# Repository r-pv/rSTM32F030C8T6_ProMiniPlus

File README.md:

# rSTM32F030C8T6 ProMini+
An ST development board based on the STM32F030C8T6 (Clock: 48MHz, Flash: 64Kb, Ram:8Kb) MCU compatible with STM32Duino (Arduino). 

Pinout:

## Files and Folders description

- **RBOARD_F030C8T6** it's the variant board for the STM32 Arduino Core.
- **rSTM32F030C8T6** it's the KiCAD 5.1.2 project.
- **rSTM32F030C8T6.schematic.pdf** the schematic.

## Install

**Update:** STCore v2.0 includes support for this MCU, if you're using STCore v2.0 you don't need to install anything.

- This requires the [STM32 core for arduino](https://github.com/stm32duino/Arduino_Core_STM32/), the ST original.
- I used this [guide to add the board](https://github.com/stm32duino/wiki/wiki/Add-a-new-variant-(board)), you can check it or continue with my suggestions to install the new board.
- Copy the **"RBOARD_F030C8T6"** folder to the Arduino **"variants"** folder, in win7 is located at: **c:\Users\\<USERNAME\>\AppData\Local\Arduino15\packages\STM32\hardware\stm32\1.6.1\variants**
- Edit the **"boards.txt"** file, in win7 is located at a lever up than the "variants" folder, search for the **F030F4** board and add the lines to leave it as I show you next:

```
# DEMO_F030F4 board
# Support: Serial1 (USART1 on PA3, PA2)
GenF0.menu.pnum.DEMO_F030F4=STM32F030F4 Demo board
GenF0.menu.pnum.DEMO_F030F4.upload.maximum_data_size=4096
GenF0.menu.pnum.DEMO_F030F4.upload.maximum_size=16384
GenF0.menu.pnum.DEMO_F030F4.build.mcu=cortex-m0
GenF0.menu.pnum.DEMO_F030F4.build.board=DEMO_F030F4
GenF0.menu.pnum.DEMO_F030F4.build.series=STM32F0xx
GenF0.menu.pnum.DEMO_F030F4.build.product_line=STM32F030x6
GenF0.menu.pnum.DEMO_F030F4.build.variant=DEMO_F030F4
GenF0.menu.pnum.DEMO_F030F4.build.cmsis_lib_gcc=arm_cortexM0l_math

# RBOARD_F030C8T6 board
# Support: Serial1 (USART1 on PA3, PA2)
GenF0.menu.pnum.RBOARD_F030C8T6=STM32F030C8 STProMiniPlus
GenF0.menu.pnum.RBOARD_F030C8T6.upload.maximum_data_size=8192
GenF0.menu.pnum.RBOARD_F030C8T6.upload.maximum_size=65536
GenF0.menu.pnum.RBOARD_F030C8T6.build.mcu=cortex-m0
GenF0.menu.pnum.RBOARD_F030C8T6.build.board=RBOARD_F030C8T6
GenF0.menu.pnum.RBOARD_F030C8T6.build.series=STM32F0xx
GenF0.menu.pnum.RBOARD_F030C8T6.build.product_line=STM32F030x8
GenF0.menu.pnum.RBOARD_F030C8T6.build.variant=RBOARD_F030C8T6
GenF0.menu.pnum.RBOARD_F030C8T6.build.cmsis_lib_gcc=arm_cortexM0l_math
```

## The real board

## Running some tests

The **ProMini+** running the Adafruit ILI9341 library over hardware SPI.

_Video in progress..._

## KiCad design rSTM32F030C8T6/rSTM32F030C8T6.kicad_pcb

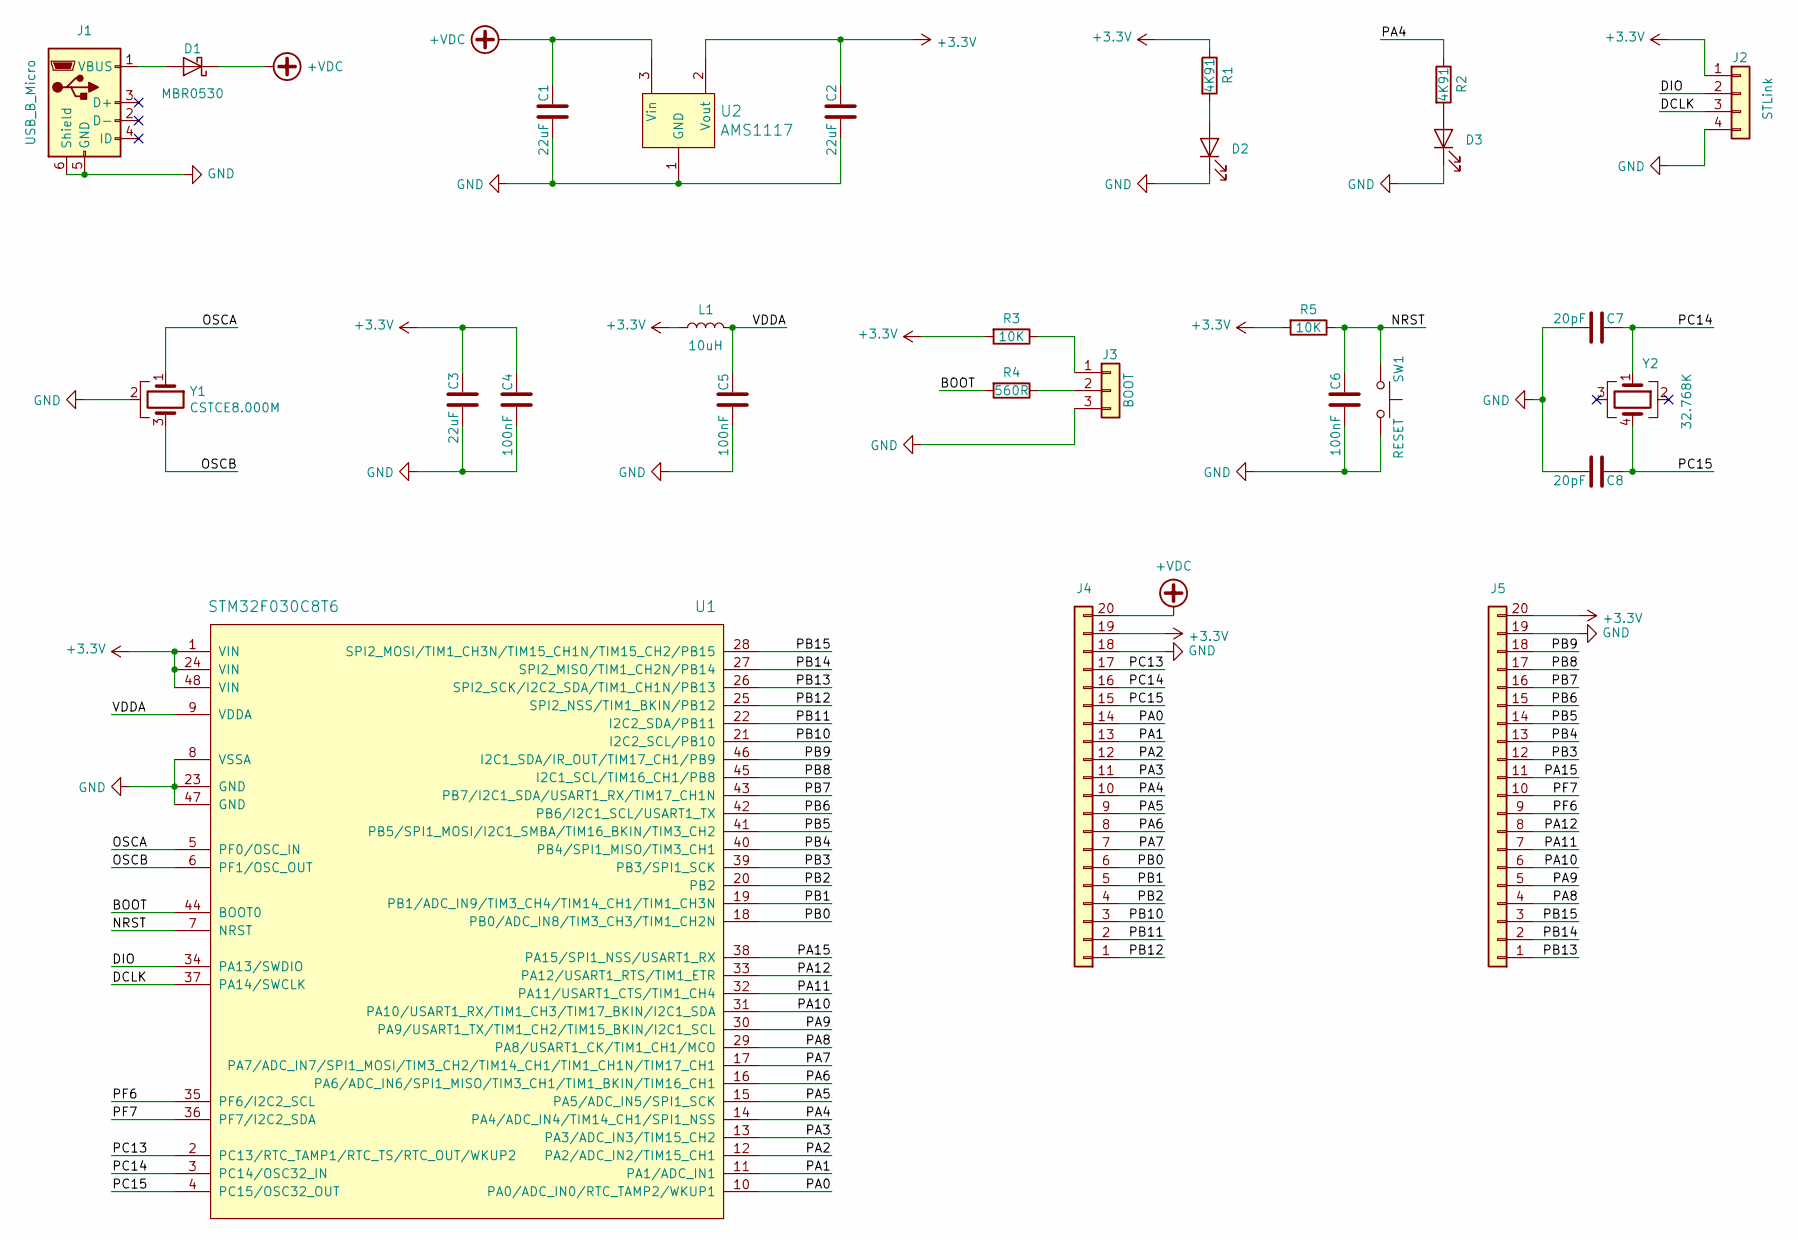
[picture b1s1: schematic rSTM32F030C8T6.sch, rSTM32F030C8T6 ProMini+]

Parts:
C1, C2, C3: 22uF; C_0805
C4, C5, C6: 100nF; C_0805
C7, C8: 20pF; C_0805
D1: MBR0530; D_SOD-123
D2, D3: LED; LED_0805
J1: USB_B_Micro; USB_Micro-B_Molex_47346-0001
J2: STLink; Pin_Header_Straight_1x04_Pitch2.54mm
J3: BOOT; Pin_Header_Straight_1x03_Pitch2.54mm
J4, J5: Pin_Header_Straight_1x20_Pitch2.54mm
L1: 10uH; L_0805
R1, R2: 4K91; R_0603
R3, R5: 10K; R_0603
R4: 560R; R_0603
SW1: RESET; Switch_SMD_5.2x6.4_reset
U1: STM32F030C8T6; LQFP-48_7x7mm_Pitch0.5mm
U2: AMS1117; SOT-223-3_TabPin2
Y1: CSTCE8.000M; Crystal_CSTCE_3pin_3.2x1.3
Y2: 32.768K; Crystal_4pin_SMD_2.5x4.6

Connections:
+3V3: C2.1, C3.1, C4.2, J2.1, J4.19, J5.20, L1.1, R1.1, R3.2, R5.2, U1.1 (VIN), U1.24 (VIN), U1.48 (VIN), U2.2 (Vout)
+VDC: C1.1, D1.1 (K), J4.20, U2.3 (Vin)
/BOOT: R4.2, U1.44 (BOOT0)
/DCLK: J2.3, U1.37 (PA14/SWCLK)
/DIO: J2.2, U1.34 (PA13/SWDIO)
/NRST: C6.1, R5.1, SW1.1, U1.7 (NRST)
/OSCA: U1.5 (PF0/OSC_IN), Y1.1
/OSCB: U1.6 (PF1/OSC_OUT), Y1.3
/PA0: J4.14, U1.10 (PA0/ADC_IN0/RTC_TAMP2/WKUP1)
/PA1: J4.13, U1.11 (PA1/ADC_IN1)
/PA2: J4.12, U1.12 (PA2/ADC_IN2/TIM15_CH1)
/PA3: J4.11, U1.13 (PA3/ADC_IN3/TIM15_CH2)
/PA4: J4.10, R2.1, U1.14 (PA4/ADC_IN4/TIM14_CH1/SPI1_NSS)
/PA5: J4.9, U1.15 (PA5/ADC_IN5/SPI1_SCK)
/PA6: J4.8, U1.16 (PA6/ADC_IN6/SPI1_MISO/TIM3_CH1/TIM1_BKI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)
/PA7: J4.7, U1.17 (PA7/ADC_IN7/SPI1_MOSI/TIM3_CH2/TIM14_CH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)
/PA8: J5.4, U1.29 (PA8/USART1_CK/TIM1_CH1/MCO)
/PA9: J5.5, U1.30 (PA9/USART1_TX/TIM1_CH2/TIM15_BKIN/I2C1_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)
/PA10: J5.6, U1.31 (PA10/USART1_RX/TIM1_CH3/TIM17_BKIN/I2C1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)
/PA11: J5.7, U1.32 (PA11/USART1_CTS/TIM1_CH4)
/PA12: J5.8, U1.33 (PA12/USART1_RTS/TIM1_ETR)
/PA15: J5.11, U1.38 (PA15/SPI1_NSS/USART1_RX)
/PB0: J4.6, U1.18 (PB0/ADC_IN8/TIM3_CH3/TIM1_CH2N)
/PB1: J4.5, U1.19 (PB1/ADC_IN9/TIM3_CH4/TIM14_CH1/TIM1_CH3N)
/PB2: J4.4, U1.20 (PB2)
/PB3: J5.12, U1.39 (PB3/SPI1_SCK)
/PB4: J5.13, U1.40 (PB4/SPI1_MISO/TIM3_CH1)
/PB5: J5.14, U1.41 (PB5/SPI1_MOSI/I2C1_SMBA/TIM16_BKIN/TIM3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)
/PB6: J5.15, U1.42 (PB6/I2C1_SCL/USART1_TX)
/PB7: J5.16, U1.43 (PB7/I2C1_SDA/USART1_RX/TIM17_CH1N)
/PB8: J5.17, U1.45 (I2C1_SCL/TIM16_CH1/PB8)
/PB9: J5.18, U1.46 (I2C1_SDA/IR_OUT/TIM17_CH1/PB9)
/PB10: J4.3, U1.21 (I2C2_SCL/PB10)
/PB11: J4.2, U1.22 (I2C2_SDA/PB11)
/PB12: J4.1, U1.25 (SPI2_NSS/TIM1_BKIN/PB12)
/PB13: J5.1, U1.26 (SPI2_SCK/I2C2_SDA/TIM1_CH1N/PB13)
/PB14: J5.2, U1.27 (SPI2_MISO/TIM1_CH2N/PB14)
/PB15: J5.3, U1.28 (SPI2_MOSI/TIM1_CH3N/TIM15_CH1N/TIM15_CH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)
/PC13: J4.17, U1.2 (PC13/RTC_TAMP1/RTC_TS/RTC_OUT/WKUP2)
/PC14: C7.1, J4.16, U1.3 (PC14/OSC32_IN), Y2.1
/PC15: C8.1, J4.15, U1.4 (PC15/OSC32_OUT), Y2.4
/PF6: J5.9, U1.35 (PF6/I2C2_SCL)
/PF7: J5.10, U1.36 (PF7/I2C2_SDA)
/VDDA: C5.2, L1.2, U1.9 (VDDA)
GND: C1.2, C2.2, C3.2, C4.1, C5.1, C6.2, C7.2, C8.2, D2.1 (K), D3.1 (K), J1.5 (GND), J1.6 (Shield), J2.4, J3.3, J4.18, J5.19, SW1.2, U1.8 (VSSA), U1.23 (GND), U1.47 (GND), U2.1 (GND), Y1.2
unnamed: D1.2 (A), J1.1 (VBUS)
unnamed: D2.2 (A), R1.2
unnamed: D3.2 (A), R2.2
unnamed: J3.1, R3.1
unnamed: J3.2, R4.1

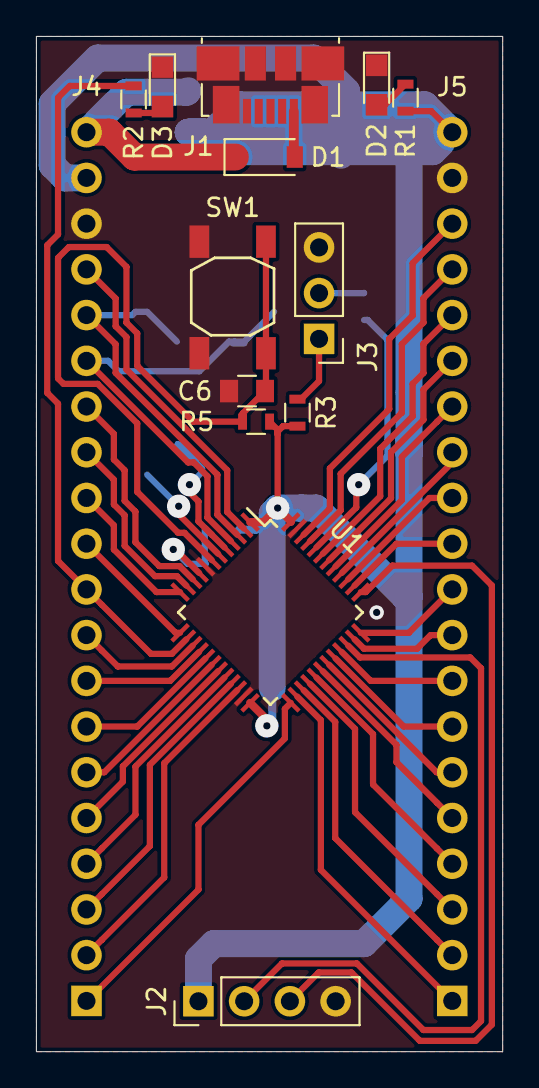
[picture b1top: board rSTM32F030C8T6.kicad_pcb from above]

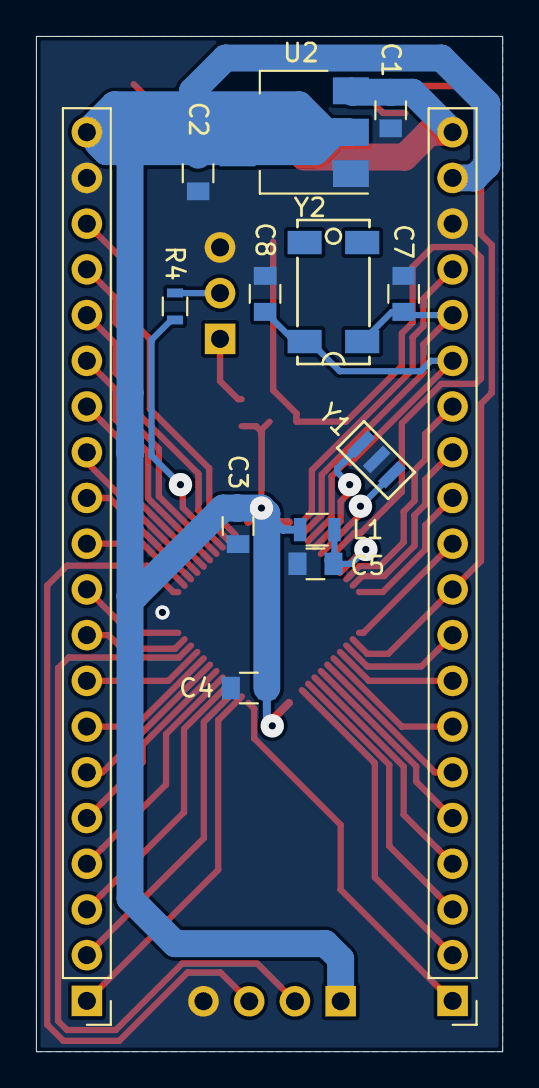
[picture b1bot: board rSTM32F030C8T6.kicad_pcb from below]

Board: 2 copper layers, 25.9 x 56.4 mm, 27 parts (14 on the bottom side), 50 nets.

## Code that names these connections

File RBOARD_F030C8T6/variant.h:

/*
 *******************************************************************************
 * Copyright (c) 2017, STMicroelectronics
 * All rights reserved.
 *
 * Redistribution and use in source and binary forms, with or without
 * modification, are permitted provided that the following conditions are met:
 *
 * 1. Redistributions of source code must retain the above copyright notice,
 *    this list of conditions and the following disclaimer.
 * 2. Redistributions in binary form must reproduce the above copyright notice,
 *    this list of conditions and the following disclaimer in the documentation
 *    and/or other materials provided with the distribution.
 * 3. Neither the name of STMicroelectronics nor the names of its contributors
 *    may be used to endorse or promote products derived from this software
 *    without specific prior written permission.
 *
 * THIS SOFTWARE IS PROVIDED BY THE COPYRIGHT HOLDERS AND CONTRIBUTORS "AS IS"
 * AND ANY EXPRESS OR IMPLIED WARRANTIES, INCLUDING, BUT NOT LIMITED TO, THE
 * IMPLIED WARRANTIES OF MERCHANTABILITY AND FITNESS FOR A PARTICULAR PURPOSE ARE
 * DISCLAIMED. IN NO EVENT SHALL THE COPYRIGHT HOLDER OR CONTRIBUTORS BE LIABLE
 * FOR ANY DIRECT, INDIRECT, INCIDENTAL, SPECIAL, EXEMPLARY, OR CONSEQUENTIAL
 * DAMAGES (INCLUDING, BUT NOT LIMITED TO, PROCUREMENT OF SUBSTITUTE GOODS OR
 * SERVICES; LOSS OF USE, DATA, OR PROFITS; OR BUSINESS INTERRUPTION) HOWEVER
 * CAUSED AND ON ANY THEORY OF LIABILITY, WHETHER IN CONTRACT, STRICT LIABILITY,
 * OR TORT (INCLUDING NEGLIGENCE OR OTHERWISE) ARISING IN ANY WAY OUT OF THE USE
 * OF THIS SOFTWARE, EVEN IF ADVISED OF THE POSSIBILITY OF SUCH DAMAGE.
 *******************************************************************************
 */
#ifndef _VARIANT_ARDUINO_STM32_
#define _VARIANT_ARDUINO_STM32_

/*----------------------------------------------------------------------------
 *        Headers
 *----------------------------------------------------------------------------*/
#ifdef __cplusplus
extern "C"{
#endif // __cplusplus

/*----------------------------------------------------------------------------
 *        Pins
 *----------------------------------------------------------------------------*/
//.with.the.USB.on.the.bottom.and.left-to-right-to-top.naming;
// Left.Side
#define PB13   0
#define PB14   1
#define PB15   2
#define PA8    3
#define PA9    4
#define PA10   5
#define PA11   6
#define PA12   7
#define PF6    8
#define PF7    9
#define PA15   10
#define PB3    11
#define PB4    12
#define PB5    13
#define PB6    14
#define PB7    15
#define PB8    16
#define PB9    17
// Bottom.side
//USB
// Right.side
#define PC13   18
#define PC14   19
#define PC15   20
#define PA0    21
#define PA1    22
#define PA2    23
#define PA3    24
#define PA4    25
#define PA5    26
#define PA6    27
#define PA7    28
#define PB0    29
#define PB1    30
#define PB2    31
#define PB10   32
#define PB11   33
#define PB12   34
// top.side.stlink
#define PA13   35
#define PA14   36

// Define pin names to match digital pin number --> Dx
// It could be used with preprocessor tests (e.g. #if PXn == 3)
// so an enum will not work.
// !!!
// !!! Copy the digitalPin[] array from the variant.cpp
// !!! and remove all '_': PX_n --> PXn
// !!! For NC, comment the line to warn x pin number is NC
// !!! // x is NC
// !!! For duplicated pin name, comment the line to warn x pin number
// !!! is PXn which is already defined with y pin number
// !!! // x is PXn (y)
// !!! Ex:
// !!! ...
// !!! #define PA4  20 // A14
// !!! #define PB4  21
// !!! #define PB5  22
// !!! #define PB3  23
// !!! // 24 is PA4 (20)
// !!! // 25 is PB4 (21)
// !!! #define PA2  26 // A15
// !!! ...
//#define PXn x

// This must be a literal
// It is used with preprocessor tests (e.g. #if NUM_DIGITAL_PINS > 3)
// so an enum will not work.
#define NUM_DIGITAL_PINS        47

// Allow to define Arduino style alias for analog input pin number --> Ax
// All pins are digital, analog inputs are a subset of digital pins
// and must be contiguous to be able to loop on each value
// This must be a literal with a value less than or equal to MAX_ANALOG_INPUTS
// defined in pin_arduino.h
// It is used with preprocessor tests (e.g. #if NUM_ANALOG_INPUTS > 3)
// so an enum will not work.
// !!!
// !!! It must be aligned with the number of analog PinName
// !!! defined in digitalPin[] array in variant.cpp
// !!!
#define NUM_ANALOG_INPUTS       10
// Define digital pin number of the first analog input  (i.e. which digital pin is A0)
// First analog pin value (A0) must be greater than or equal to NUM_ANALOG_INPUTS
#define NUM_ANALOG_FIRST        21

// Below ADC, DAC and PWM definitions already done in the core
// Could be redefined here if needed
// ADC resolution is 12bits
//#define ADC_RESOLUTION          12
//#define DACC_RESOLUTION         12

// PWM resolution
//#define PWM_RESOLUTION          8
//#define PWM_FREQUENCY           1000
//#define PWM_MAX_DUTY_CYCLE      255

// On-board LED pin number
#define LED_BUILTIN             PA4
#define LED_GREEN               LED_BUILTIN

// On-board user button
#define USER_BTN                x

// Below SPI and I2C definitions already done in the core
// Could be redefined here if differs from the default one
// SPI Definitions
// SPI Definitions
#define PIN_SPI_SS              PA4
#define PIN_SPI_MOSI            PA7
#define PIN_SPI_MISO            PA6
#define PIN_SPI_SCK             PA5

// I2C Definitions
#define PIN_WIRE_SDA            PB7 // Default for Arduino connector compatibility
#define PIN_WIRE_SCL            PB6  // Default for Arduino connector compatibility

// Timer Definitions
// Do not use timer used by PWM pins when possible. See PinMap_PWM.
#define TIMER_TONE              TIM17

// Do not use basic timer: OC is required
#define TIMER_SERVO             TIM16  //TODO: advanced-control timers don't work

// UART Definitions
#define SERIAL_UART_INSTANCE    1
// Default pin used for 'Serial' instance
// Mandatory for Firmata
#define PIN_SERIAL_RX           PA10
#define PIN_SERIAL_TX           PA9

// UART Definitions
// Define here Serial instance number to map on Serial generic name
//#define SERIAL_UART_INSTANCE    x //ex: 2 for Serial2 (USART2)
// DEBUG_UART could be redefined to print on another instance than 'Serial'
//#define DEBUG_UART              ((USART_TypeDef *) U(S)ARTX) // ex: USART3
// DEBUG_UART baudrate, default: 9600 if not defined
//#define DEBUG_UART_BAUDRATE     x
// DEBUG_UART Tx pin name, default: the first one found in PinMap_UART_TX for DEBUG_UART
//#define DEBUG_PINNAME_TX        PX_n // PinName used for TX


// Optional PIN_SERIALn_RX and PIN_SERIALn_TX where 'n' is the U(S)ART number
// Used when user instanciate a hardware Serial using its peripheral name.
// Example: HardwareSerial mySerial(USART3);
// will use PIN_SERIAL3_RX and PIN_SERIAL3_TX if defined.
//#define PIN_SERIALn_RX          x // For U(S)ARTn RX
//#define PIN_SERIALn_TX          x // For U(S)ARTn TX
//#define PIN_SERIALLP1_RX        x // For LPUART1 RX
//#define PIN_SERIALLP1_TX        x // For LPUART1 TX

// SD card slot Definitions
// SD detect signal can be defined if required
//#define SD_DETECT_PIN           x
// SD Read/Write timeout, default value defined in STM32SD library
//#define SD_DATATIMEOUT          x

#ifdef __cplusplus
} // extern "C"
#endif
/*----------------------------------------------------------------------------
 *        Arduino objects - C++ only
 *----------------------------------------------------------------------------*/

#ifdef __cplusplus
// These serial port names are intended to allow libraries and architecture-neutral
// sketches to automatically default to the correct port name for a particular type
// of use.  For example, a GPS module would normally connect to SERIAL_PORT_HARDWARE_OPEN,
// the first hardware serial port whose RX/TX pins are not dedicated to another use.
//
// SERIAL_PORT_MONITOR        Port which normally prints to the Arduino Serial Monitor
//
// SERIAL_PORT_USBVIRTUAL     Port which is USB virtual serial
//
// SERIAL_PORT_LINUXBRIDGE    Port which connects to a Linux system via Bridge library
//
// SERIAL_PORT_HARDWARE       Hardware serial port, physical RX & TX pins.
//
// SERIAL_PORT_HARDWARE_OPEN  Hardware serial ports which are open for use.  Their RX & TX
//                            pins are NOT connected to anything by default.
#define SERIAL_PORT_MONITOR     Serial
#define SERIAL_PORT_HARDWARE    Serial
#endif

#endif /* _VARIANT_ARDUINO_STM32_ */

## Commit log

2019-09-10 Schematic
2019-09-10 stm32duino variant.
2019-09-11 HAL_conf it's do required by the arduino ide.
2019-09-11 fixing some errors.
2019-09-11 info.
2019-09-12 small fix.
2019-09-23 Pinout update, added ADC and PWM pins.
2019-10-17 Small correction.
2019-10-24 Fixed a bug with the analogs.
    Fixed a mistake I made.
2020-05-17 PinOut updated, added: SPI2, UART2 and I2C2
2021-05-03 ST Core 2.0 notice.
2021-05-03 ST Core v2.0 notice.
